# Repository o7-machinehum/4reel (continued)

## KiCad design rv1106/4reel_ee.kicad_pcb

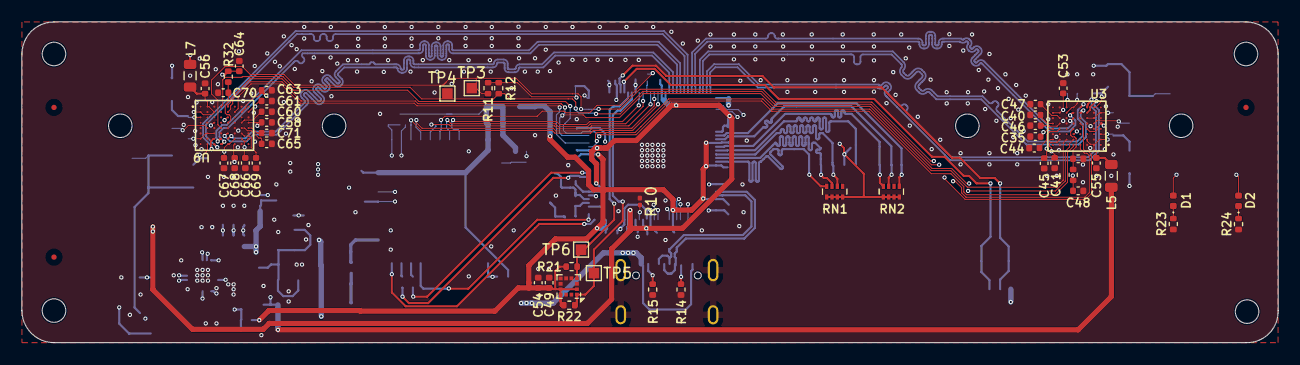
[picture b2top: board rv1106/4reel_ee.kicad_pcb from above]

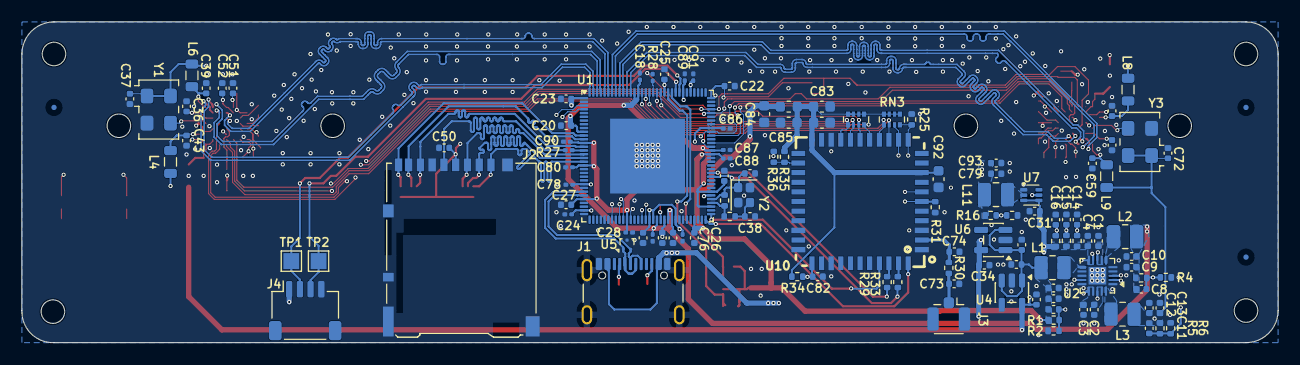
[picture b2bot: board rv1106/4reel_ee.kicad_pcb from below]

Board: 4 copper layers, 117.5 x 30.0 mm, 179 parts (120 on the bottom side), 102 nets.

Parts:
C1, C14, C15, C16, C36, C37, C41, C42, C45, C49, C51, C52, C53, C61, C62, C63, C66, C67, C68, C70, C72: 100nF; C_0402_1005Metric
C2, C3, C4, C5, C7, C9, C10, C12, C13, C17, C19, C20, C21, C22, C23, C25, C26, C27, C31, C50, C54, C77, C79, C93: 10uF; C_0402_1005Metric
C6, C8, C11: 220pF; C_0402_1005Metric
C18, C24, C28, C75, C76, C78, C80, C86, C87, C88, C89, C90, C91: 100nF; C_0201_0603Metric
C29, C30, C33, C34, C35, C39, C40, C43, C44, C46, C47, C48, C55, C56, C57, C58, C59, C60, C64, C65, C69, C71: 1uF; C_0402_1005Metric
C32, C38: 10pF; C_0402_1005Metric
C73, C74, C82: NC; C_0402_1005Metric
C81, C83, C84, C85, C92: 10uF; C_0603_1608Metric
D1, D2: LED; LED_0402_1005Metric
FID1, FID2, FID3, FID4, FID5, FID6: Fiducial; Fiducial_0.5mm_Mask1.5mm
H1, H2, H3, H4: M2; MountingHole_2.2mm_M2
J1: USB_C_Receptacle_USB2.0_16P; USB_C_Receptacle_GCT_USB4105-xx-A_16P_TopMnt_Horizontal
J2: Micro_SD_Card_Det2; microSD_HC_Hirose_DM3AT-SF-PEJM5
J3: Conn_Coaxial; U.FL_Hirose_U.FL-R-SMT-1_Vertical
J4: JST; JST_SH_SM04B-SRSS-TB_1x04-1MP_P1.00mm_Horizontal
L1, L2, L3: 1.5uH; L_1008_2520Metric
L4, L5, L6, L7, L8, L9: 3u3/0.9A; L_0805_2012Metric
L10: 120R@100MHz; L_0603_1608Metric
L11: 1uH; L_1008_2520Metric
MP1, MP2: Camera_Lens_20mm
R1: 40.2k; R_0402_1005Metric
R2: 9.1k; R_0402_1005Metric
R3: 47k; R_0402_1005Metric
R4, R6, R9, R16, R34: 100k; R_0402_1005Metric
R5, R7: 200k; R_0402_1005Metric
R8, R35: 10k; R_0402_1005Metric
R10: 240R; R_0201_0603Metric
R11, R12, R21, R22: 4.7k; R_0402_1005Metric
R13, R30, R32, R36: 0R; R_0402_1005Metric
R14, R15: 5.6k; R_0402_1005Metric
R17: 80k; R_0402_1005Metric
R19: 22R; R_0402_1005Metric
R20: 1M; R_0402_1005Metric
R23, R24, R29, R33: 1k; R_0402_1005Metric
R25: 10K; R_0402_1005Metric
R27, R28: 22R; R_0201_0603Metric
R31: 100K; R_0402_1005Metric
RN1, RN2: 47k; R_Array_Concave_4x0402
RN3, RN4: 10k; R_Array_Convex_4x0402
TP1, TP2: TestPoint; TestPoint_Pad_1.5x1.5mm
TP3, TP4, TP5, TP6: TestPoint; TestPoint_Pad_1.0x1.0mm
U1: RV1106G3; Rockchip_QFN-128-1EP_12.3x12.3mm_P0.35mm_EP7x7mm
U2: EA3036C; QFN-20-1EP_3x3mm_P0.4mm_EP1.65x1.65mm
U3, U9: ImageSensor_OV9281; OV9281
U4: TLV73312PDBV; SOT-23-5
U5: TPD2EUSB30; Texas_DRT-3
U6: TLV73328PDBV; SOT-23-5
U7: TPS62A01ADRL; SOT-563
U8: LIS2HH12; LGA-12_2x2mm_P0.5mm
U10: RTL8723DS; RTL8723
Y1, Y3: TXC-7C; Oscillator_SMD_TXC_7C-4Pin_5.0x3.2mm
Y2: 24Mhz; Crystal_SMD_2016-4Pin_2.0x1.6mm

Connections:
+0V9: C8.1, C9.1, C10.1, C17.1, C18.1, C19.1, C20.1, C75.1, C87.1, C89.1, L2.2, R3.1, U1.10 (DVDD_1), U1.51 (DVDD_2), U1.54 (DVDD_3), U1.55 (DVDD_4), U1.67 (PMU_DVDD0V9), U1.71 (OSC_PLL_DVDD), U1.82 (DVDD_5), U1.103 (DVDD_6), U1.115 (CPU_DVDD), U1.116 (DVDD_7)
+1V2: C30.1, L5.1, L7.1, U4.5 (OUT)
+1V8: C11.1, C12.1, C13.1, C21.1, C22.1, C23.1, C24.1, C37.1, C72.1, C78.1, C86.1, L3.2, L6.1, L9.1, R5.1, R11.1, R12.1, U1.1 (MIPI_AVDD1V8), U1.24 (SARADC_USB_AVDD1V8), U1.31 (CODEC_AVDD1V8), U1.53 (DDR_PLL_AVDD1V8), U1.70 (OSC_AVDD1V8), U1.88 (GPIO6_VCC), U1.96 (OTP_AVDD1V8), Y1.1 (EN), Y1.4 (Vdd), Y3.1 (EN), Y3.4 (Vdd)
+1V35: C76.1, C77.1, C79.1, C93.1, L11.2, R16.1, U1.49 (DDR_VDDQ_1), U1.50 (DDR_VDDQ_2), U1.56 (DDR_VDDQ_3)
+2V8: C34.1, L4.1, L8.1, U6.5 (OUT)
+3.3VA: C81.1, C83.1, C85.1, C92.1, L10.2, R34.2, R35.2, RN3.5 (R4.2), RN3.6 (R3.2), RN3.7 (R2.2), RN3.8 (R1.2), RN4.5 (R4.2), RN4.6 (R3.2), RN4.7 (R2.2), RN4.8 (R1.2), U10.9 (VBAT), U10.22 (VDD_IO)
+3V3: C5.1, C6.1, C7.1, C25.1, C26.1, C27.1, C28.1, C29.1, C33.1, C49.1, C50.1, C54.1, C80.1, C84.1, C88.1, C90.1, C91.1, J2.4 (VDD), L1.2, L10.1, R1.1, R21.1, R22.1, RN1.5 (R4.2), RN1.6 (R3.2), RN1.7 (R2.2), RN1.8 (R1.2), RN2.5 (R4.2), RN2.6 (R3.2), RN2.7 (R2.2), RN2.8 (R1.2), U1.13 (GPIO4_VCC), U1.19 (RTC_AVDD3V3), U1.28 (USB_AVDD3V3), U1.43 (GPIO3_VCC), U1.61 (PMU_VCC3V3), U1.81 (GPIO1_VCC3V3), U1.101 (ETH_AVDD3V3), U1.108 (GPIO5_VCC), U4.1 (IN), U4.3 (EN), U6.1 (IN), U6.3 (EN), U8.2 (~CS), U8.9 (Vdd), U8.10 (Vdd_IO)
+5V: C1.1, C2.1, C3.1, C4.1, C31.1, J1.A4 (VBUS), J1.A9 (VBUS), J1.B4 (VBUS), J1.B9 (VBUS), J4.1, R7.1, R8.1, R9.1, U2.7 (VIN2), U2.10 (VIN1), U2.16 (VCC), U2.19 (VIN3), U7.3 (VIN), U7.4 (EN)
/Accelerometer/I2C3.SCL: R22.2, TP5.1 (1_1), U1.107 (UART0_RTS_M1), U8.1 (SCL/SPC)
/Accelerometer/I2C3.SDA: R21.2, TP6.1 (1_1), U1.106 (UART0_CTS_M1), U8.4 (SDA/SDI)
/MPU/BT_HOST_WAKE: U1.44 (FSPI_D2), U10.7 (BT_HOST_WAKE)
/MPU/BT_LPO: R36.1, U1.39 (FSPI_D3)
/MPU/BT_WAKE: R31.2, U1.47 (FSPI_CS0), U10.6 (BT_WAKE)
/MPU/I2C4.SCL: R11.2, TP3.1 (1_1), U1.93 (VO_LCDC_D5), U3.E4 (SCL), U9.E4 (SCL)
/MPU/I2C4.SDA: R12.2, TP4.1 (1_1), U1.92 (VO_LCDC_D4), U3.A4 (SDA), U9.A4 (SDA)
/MPU/LED1: D1.2 (A), U1.4 (MIPI_CLK1_OUT)
/MPU/LED2: D2.2 (A), U1.3 (VI_CIF_VSYNC_M0)
/MPU/MIPI1.CK0N: U1.125 (MIPI_CSI_RX_CK0N), U3.H4 (MDCN)
/MPU/MIPI1.CK0P: U1.126 (MIPI_CSI_RX_CK0P), U3.G4 (MDCP)
/MPU/MIPI1.D0N: U1.127 (MIPI_CSI_RX_D0N), U3.H3 (MDN0)
/MPU/MIPI1.D0P: U1.128 (MIPI_CSI_RX_D0P), U3.G3 (MDP0)
/MPU/MIPI1.D1N: U1.123 (MIPI_CSI_RX_D1N), U3.F5 (MD1N)
/MPU/MIPI1.D1P: U1.124 (MIPI_CSI_RX_D1P), U3.G5 (MDP1)
/MPU/MIPI2.CK0N: U1.119 (MIPI_CSI_RX_CK1N), U9.H4 (MDCN)
/MPU/MIPI2.CK0P: U1.120 (MIPI_CSI_RX_CK1P), U9.G4 (MDCP)
/MPU/MIPI2.D0N: U1.121 (MIPI_CSI_RX_D2N), U9.H3 (MDN0)
/MPU/MIPI2.D0P: U1.122 (MIPI_CSI_RX_D2P), U9.G3 (MDP0)
/MPU/MIPI2.D1N: U1.117 (MIPI_CSI_RX_D3N), U9.F5 (MD1N)
/MPU/MIPI2.D1P: U1.118 (MIPI_CSI_RX_D3P), U9.G5 (MDP1)
/MPU/SDMMC1.CLK: J2.5 (CLK), R27.2
/MPU/SDMMC1.CMD: J2.3 (CMD), RN1.2 (R2.1), U1.16 (SDMMC0_CMD)
/MPU/SDMMC1.D0: J2.7 (DAT0), RN2.4 (R4.1), U1.14 (SDMMC0_D0)
/MPU/SDMMC1.D1: J2.8 (DAT1), RN2.3 (R3.1), U1.12 (SDMMC0_D1)
/MPU/SDMMC1.D2: J2.1 (DAT2), RN1.4 (R4.1), U1.18 (SDMMC0_D2)
/MPU/SDMMC1.D3: J2.2 (DAT3/CD), RN1.3 (R3.1), U1.17 (SDMMC0_D3)
/MPU/SDMMC1.DET: J2.9 (DET_B), RN2.1 (R1.1), U1.11 (SDMMC0_DET)
/MPU/SDMMC2.CLK: R28.2, RN4.3 (R3.1), U10.17 (SD_CLK)
/MPU/SDMMC2.CMD: RN4.4 (R4.1), U1.112 (SDMMC1_CMD_M0), U10.16 (SD_CMD)
/MPU/SDMMC2.D0: RN4.2 (R2.1), U1.110 (SDMMC1_D0_M0), U10.18 (SD_D0)
/MPU/SDMMC2.D1: RN4.1 (R1.1), U1.109 (SDMMC1_D1_M0), U10.19 (SD_D1)
/MPU/SDMMC2.D2: RN3.2 (R2.1), U1.114 (SDMMC1_D2_M0), U10.14 (SD_D2)
/MPU/SDMMC2.D3: RN3.1 (R1.1), U1.113 (SDMMC1_D3_M0), U10.15 (SD_D3)
/MPU/STROBE1: U1.83 (VO_LCDC_D1), U3.B6 (STROBE)
/MPU/STROBE2: U1.84 (VO_LCDC_D0), U9.B6 (STROBE)
/MPU/UART1.RXD: R29.1, U1.76 (UART1_RX_M0)
/MPU/UART1.TXD: R33.1, U1.75 (UART1_TX_M0)
/MPU/UART1.~CTS: U1.65 (I2C1_SDA_M0), U10.41 (UART_RTS_N)
/MPU/UART1.~RTS: U1.64 (I2C1_SCL_M0), U10.44 (UART_CTS_N)
/MPU/UART_RX: J4.3, TP2.1 (1_1), U1.105 (UART0_RX_M1)
/MPU/UART_TX: J4.2, TP1.1 (1_1), U1.104 (UART0_TX_M1)
/MPU/USB.DN: J1.A7 (D-), J1.B7 (D-), U1.26 (USB_DM), U5.1 (D+)
/MPU/USB.DP: J1.A6 (D+), J1.B6 (D+), U1.27 (USB_DP), U5.2 (D-)
/MPU/VSYNC: U1.86 (VO_LCDC_VSYNC), U3.B5 (FSIN/VSYNC), U9.B5 (FSIN/VSYNC)
/MPU/WL_HOST_WAKE: RN3.3 (R3.1), U1.41 (FSPI_D0), U10.13 (WL_HOST_WAKE)
/MPU/WL_REG_ON: R25.2, RN3.4 (R4.1), U1.42 (FSPI_D1), U10.12 (WL_REG_ON)
/MPU/XSHUTDOWN: U1.87 (VO_LCDC_HSYNC), U3.A5 (XSHUTDOWN), U9.A5 (XSHUTDOWN)
/MPU/~BT_RST: C82.1, R34.1, U1.48 (FSPI_CLK), U10.34 (BT_RST_N)
/OV9281/AVDD: C43.1, C45.1, C48.1, C53.1, L4.2, R13.2, U3.B8 (AVDD), U3.C1 (AVDD), U3.G7 (AVDD), U3.G8 (AVDD)
/OV9281/DOVDD: C39.1, C41.1, C51.1, L6.2, U3.B7 (DOVDD), U3.D3 (DOVDD), U3.E1 (SID), U3.H2 (DOVDD), U3.H6 (DOVDD)
/OV9281/DVDD: C35.1, C36.1, C52.1, C55.1, L5.2, U3.A2 (DVDD), U3.B1 (DVDD), U3.B3 (DVDD), U3.C5 (DVDD), U3.D8 (DVDD), U3.F2 (DVDD), U3.F3 (EVDD), U3.G1 (DVDD), U3.G6 (DVDD), U3.H5 (EVDD)
/OV9281/VN1: C44.1, U3.D7 (VN1)
/OV9281/VN2: C46.1, U3.E7 (VN2)
/OV9281/VN3: C47.1, U3.F7 (VN3)
/OV9282/AVDD: C57.1, C61.1, C64.1, C66.1, L8.2, R32.2, U9.B8 (AVDD), U9.C1 (AVDD), U9.G7 (AVDD), U9.G8 (AVDD)
/OV9282/DOVDD: C59.1, C63.1, C68.1, L9.2, U9.B7 (DOVDD), U9.D3 (DOVDD), U9.H2 (DOVDD), U9.H6 (DOVDD)
/OV9282/DVDD: C56.1, C58.1, C62.1, C67.1, L7.2, U9.A2 (DVDD), U9.B1 (DVDD), U9.B3 (DVDD), U9.C5 (DVDD), U9.D8 (DVDD), U9.F2 (DVDD), U9.F3 (EVDD), U9.G1 (DVDD), U9.G6 (DVDD), U9.H5 (EVDD)
/OV9282/VN1: C60.1, U9.D7 (VN1)
/OV9282/VN2: C65.1, U9.E7 (VN2)
/OV9282/VN3: C69.1, U9.F7 (VN3)
/RTL8723/LPO: R35.1, R36.2, U10.24 (LPO)
GND: C1.2, C2.2, C3.2, C4.2, C5.2, C7.2, C9.2, C10.2, C12.2, C13.2, C14.2, C15.2, C16.2, C17.2, C18.2, C19.2, C20.2, C21.2, C22.2, C23.2, C24.2, C25.2, C26.2, C27.2, C28.2, C29.2, C30.2, C31.2, C32.2, C33.2, C34.2, C35.2, C36.2, C37.2, C38.1, C39.2, C40.2, C41.2, C42.2, C43.2, C44.2, C45.2, C46.2, C47.2, C48.2, C49.2, C50.2, C51.2, C52.2, C53.2, C54.2, C55.2, C56.2, C57.2, C58.2, C59.2, C60.2, C61.2, C62.2, C63.2, C64.2, C65.2, C66.2, C67.2, C68.2, C69.2, C70.2, C71.2, C72.2, C73.2, C74.2, C75.2, C76.2, C77.2, C78.2, C79.2, C80.2, C81.2, C82.2, C83.2, C84.2, C85.2, C86.2, C87.2, C88.2, C89.2, C90.2, C91.2, C92.2, C93.2, J1.A1 (GND), J1.A12 (GND), J1.B1 (GND), J1.B12 (GND), J1.SH (SHIELD), J2.6 (VSS), J2.10 (DET_A), J2.SH (SHIELD), J3.2 (Ext), J4.4, R2.2, R4.2, R6.2, R10.1, R14.1, R15.2, R17.2, R23.2, R24.2, R25.1, R31.1, U1.37 (CODEC_AVSS), U1.57 (TVSS), U1.129 (VSS), U2.1 (GND3), U2.4 (GND2), U2.5 (GND2), U2.12 (GND1), U2.13 (GND1), U2.15 (AGND), U2.17 (AGND), U2.21 (EP), U3.A3 (DOGND), U3.A7 (DOGND), U3.B2 (DOGND), U3.C8 (AGND), U3.D2 (AGND), U3.E3 (EGND), U3.E5 (EGND), U3.E6 (TM), U3.F1 (DOGND), U3.F4 (DOGND), U3.F6 (DOGND), U3.F8 (AGND), U3.G2 (DOGND), U3.H7 (AGND), U4.2 (GND), U5.3 (GND), U6.2 (GND), U7.1 (GND), U8.3 (SA0/SDO), U8.5 (RES), U8.6 (GND), U8.7 (GND), U8.8 (GND), U9.A3 (DOGND), U9.A7 (DOGND), U9.B2 (DOGND), U9.C8 (AGND), U9.D2 (AGND), U9.E1 (SID), U9.E3 (EGND), U9.E5 (EGND), U9.E6 (TM), U9.F1 (DOGND), U9.F4 (DOGND), U9.F6 (DOGND), U9.F8 (AGND), U9.G2 (DOGND), U9.H7 (AGND), U10.1 (GND), U10.3 (GND), U10.20 (GND), U10.31 (GND), U10.33 (GND), U10.36 (GND), Y1.2 (GND), Y2.2 (G), Y2.4 (G), Y3.2 (GND)
unnamed: C38.2, R19.1, Y2.3
unnamed: D1.1 (K), R23.1
unnamed: D2.1 (K), R24.1
unnamed: J1.A5 (CC1), R14.2
unnamed: J1.B5 (CC2), R15.1
unnamed: C73.1, J3.1 (In), R30.1
unnamed: R10.2, U1.52 (DRAM_ZQ)
unnamed: R19.2, R20.1, U1.68 (OSC_XIN)
unnamed: C32.1, R20.2, U1.69 (OSC_XOUT), Y2.1
unnamed: R27.1, U1.15 (SDMMC0_CLK)
unnamed: R28.1, U1.111 (SDMMC1_CLK_M0)
unnamed: C14.1, R7.2, U2.9 (EN1)
unnamed: C15.1, R8.2, U2.8 (EN2)
unnamed: C16.1, R9.2, U2.18 (EN3)
unnamed: C6.2, R1.2, R2.1, U2.14 (FB1)
unnamed: C8.2, R3.2, R4.1, U2.3 (FB2)
unnamed: C11.2, R5.2, R6.1, U2.2 (FB3)
unnamed: L1.1, U2.11 (LX1)
unnamed: L2.1, U2.6 (LX2)
unnamed: L3.1, U2.20 (LX3)
unnamed: C42.1, R13.1, U3.D5 (PVDD)
unnamed: C40.1, U3.E8 (VH)
unnamed: U3.E2 (XVCLK), Y1.3 (OUT)
unnamed: R16.2, R17.1, U7.5 (FB)
unnamed: L11.1, U7.2 (SW)
unnamed: C70.1, R32.1, U9.D5 (PVDD)
unnamed: C71.1, U9.E8 (VH)
unnamed: U9.E2 (XVCLK), Y3.3 (OUT)
unnamed: R33.2, U10.43 (UART_RXD)
unnamed: R29.2, U10.42 (UART_TXD)
unnamed: C74.1, R30.2, U10.2 (WIFI/BT_ANT)

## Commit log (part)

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2026-06-30 Initial commit.
